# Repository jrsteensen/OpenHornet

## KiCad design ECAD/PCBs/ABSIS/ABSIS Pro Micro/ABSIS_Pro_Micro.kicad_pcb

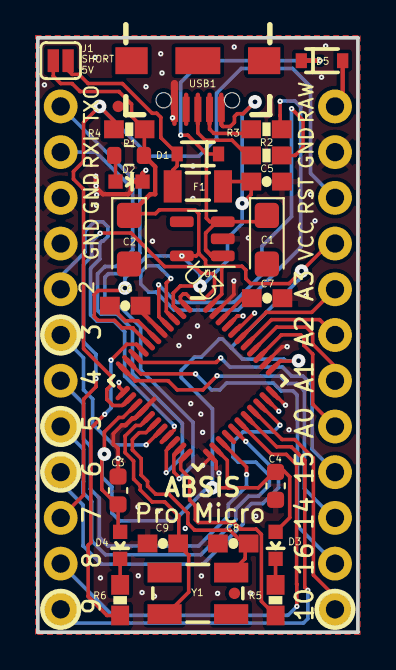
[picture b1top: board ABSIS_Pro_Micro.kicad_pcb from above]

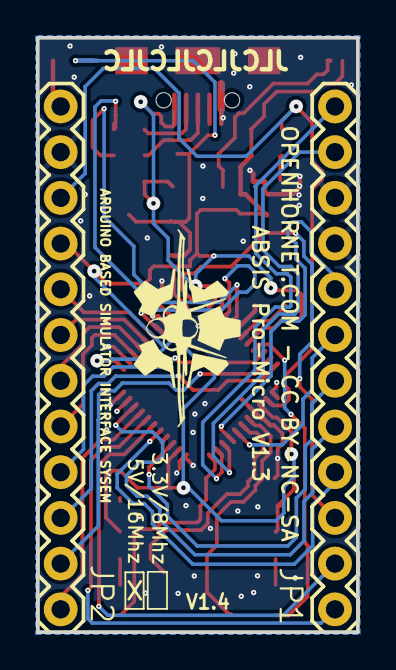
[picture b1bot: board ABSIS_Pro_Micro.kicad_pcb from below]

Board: 2 copper layers, 17.8 x 33.0 mm, 34 parts (3 on the bottom side), 38 nets.

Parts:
C1, C2: 10uF; CP_EIA-3216-18_Kemet-A
C3: 1uF; C_0603_1608Metric
C4: 0.1uF; C_0603_1608Metric
C5, C6: 1uF; 0603-CAP
C7: 0.1uF; 0603-CAP
C8, C9: 22pF; 0603-CAP
D1, D5: 1N4448WX-TP; SOD-323
D2: Red; LED-0603
D3: Green; LED-0603
D4: Yellow; LED-0603
F1: 500mA; PTC-1206
FRAME1, FRAME1#2: FRAME-LETTER; CREATIVE_COMMONS
JP1, JP2: M12PTH; 1X12
JP3, JP6: FIDUCIALUFIDUCIAL; MICRO-FIDUCIAL
JP4: LOGO-SFESK; SFE-LOGO-FLAME
LOGO: LOGO; LOGO_OH_NoText_Small
R1: 1K; R_0603_1608Metric
R2, R3: 22; 0603-RES
R4: 10K; 0603-RES
R5, R6: 330; 0603-RES
SJ1: SOLDERJUMPERNC; SJ_2S
U1: MIC5219; SOT-23-5
U3: ATMEGA32U4; QFN-44-NOPAD_1_1-OUTFAKES
USB1: ZX62-AB-5PA(31); USB-AB-MICRO-SMD-V03-IN&OUT
Y1: 16MHz; CRYSTAL-SMD-5X3

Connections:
+5V: C3.1, C4.2, C5.2, D3.A, D4.A, F1.1, JP2.4, R1.2, R4.2, U1.5 (OUT), U3.2 (UVCC), U3.7 (VBUS), U3.14 (VCC@14), U3.24 (AVCC@24), U3.34 (VCC@34), U3.44 (AVCC@44), USB1.VBUS1 (VBUS)
/A0: JP2.8, U3.36 (PF7(ADC7))
/A1: JP2.7, U3.37 (PF6(ADC6))
/A2: JP2.6, U3.38 (PF5(ADC5))
/A3: JP2.5, U3.39 (PF4(ADC4))
/AREF: C7.2, U3.42 (AREF)
/D2: JP1.8, U3.19 (PD1(SDA))
/D3: JP1.7, U3.18 (PD0(SCL))
/D4: JP1.6, U3.25 (PD4(ADC8))
/D5: JP1.5, U3.31 (PC6)
/D6: JP1.4, U3.27 (PD7(ADC10))
/D7: JP1.3, U3.1 (PE6)
/D8: JP1.2, U3.28 (PB4(ADC11))
/D9: JP1.1, U3.29 (PB5(ADC12))
/D10: JP2.12, U3.30 (PB6(ADC13))
/D14: R6.1, U3.8 (PB3(MISO))
/D+: R2.1, U3.4 (D+)
/D-: R3.1, U3.3 (D-)
/MISO: JP2.10, U3.11 (PB0(SS))
/MOSI: JP2.11, U3.10 (PB2(MOSI))
/RAW: D5.2 (A), JP2.1
/RESET: JP2.3, R4.1, U3.13 (~RESET)
/RXI: JP1.11, U3.20 (PD2(RX))
/SCK: JP2.9, U3.9 (PB1(SCK))
/TXO: JP1.12, U3.21 (PD3(TX))
GND: C3.2, C4.1, C5.1, C6.1, C7.1, C8.2, C9.2, D2.C, JP1.9, JP1.10, JP2.2, U1.2 (GND), U3.5 (UGND), U3.15 (GND@15), U3.23 (GND@23), U3.33 (PE2/~HWB), U3.35 (GND@35), U3.43 (GND@43), USB1.GND1 (GND)
unnamed: D1.1 (C), D5.1 (C), U1.1 (IN), U1.3 (EN)
unnamed: D1.2 (A), SJ1.2
unnamed: D2.A, R1.1
unnamed: D3.C, R5.2
unnamed: D4.C, R6.2
unnamed: F1.2, SJ1.1
unnamed: R5.1, U3.22 (PD5)
unnamed: C6.2, U3.6 (UCAP)
unnamed: C8.1, U3.17 (XTAL1), Y1.3 (2)
unnamed: C9.1, U3.16 (XTAL2), Y1.1
unnamed: R2.2, USB1.D+1 (D+)
unnamed: R3.2, USB1.D-1 (D-)

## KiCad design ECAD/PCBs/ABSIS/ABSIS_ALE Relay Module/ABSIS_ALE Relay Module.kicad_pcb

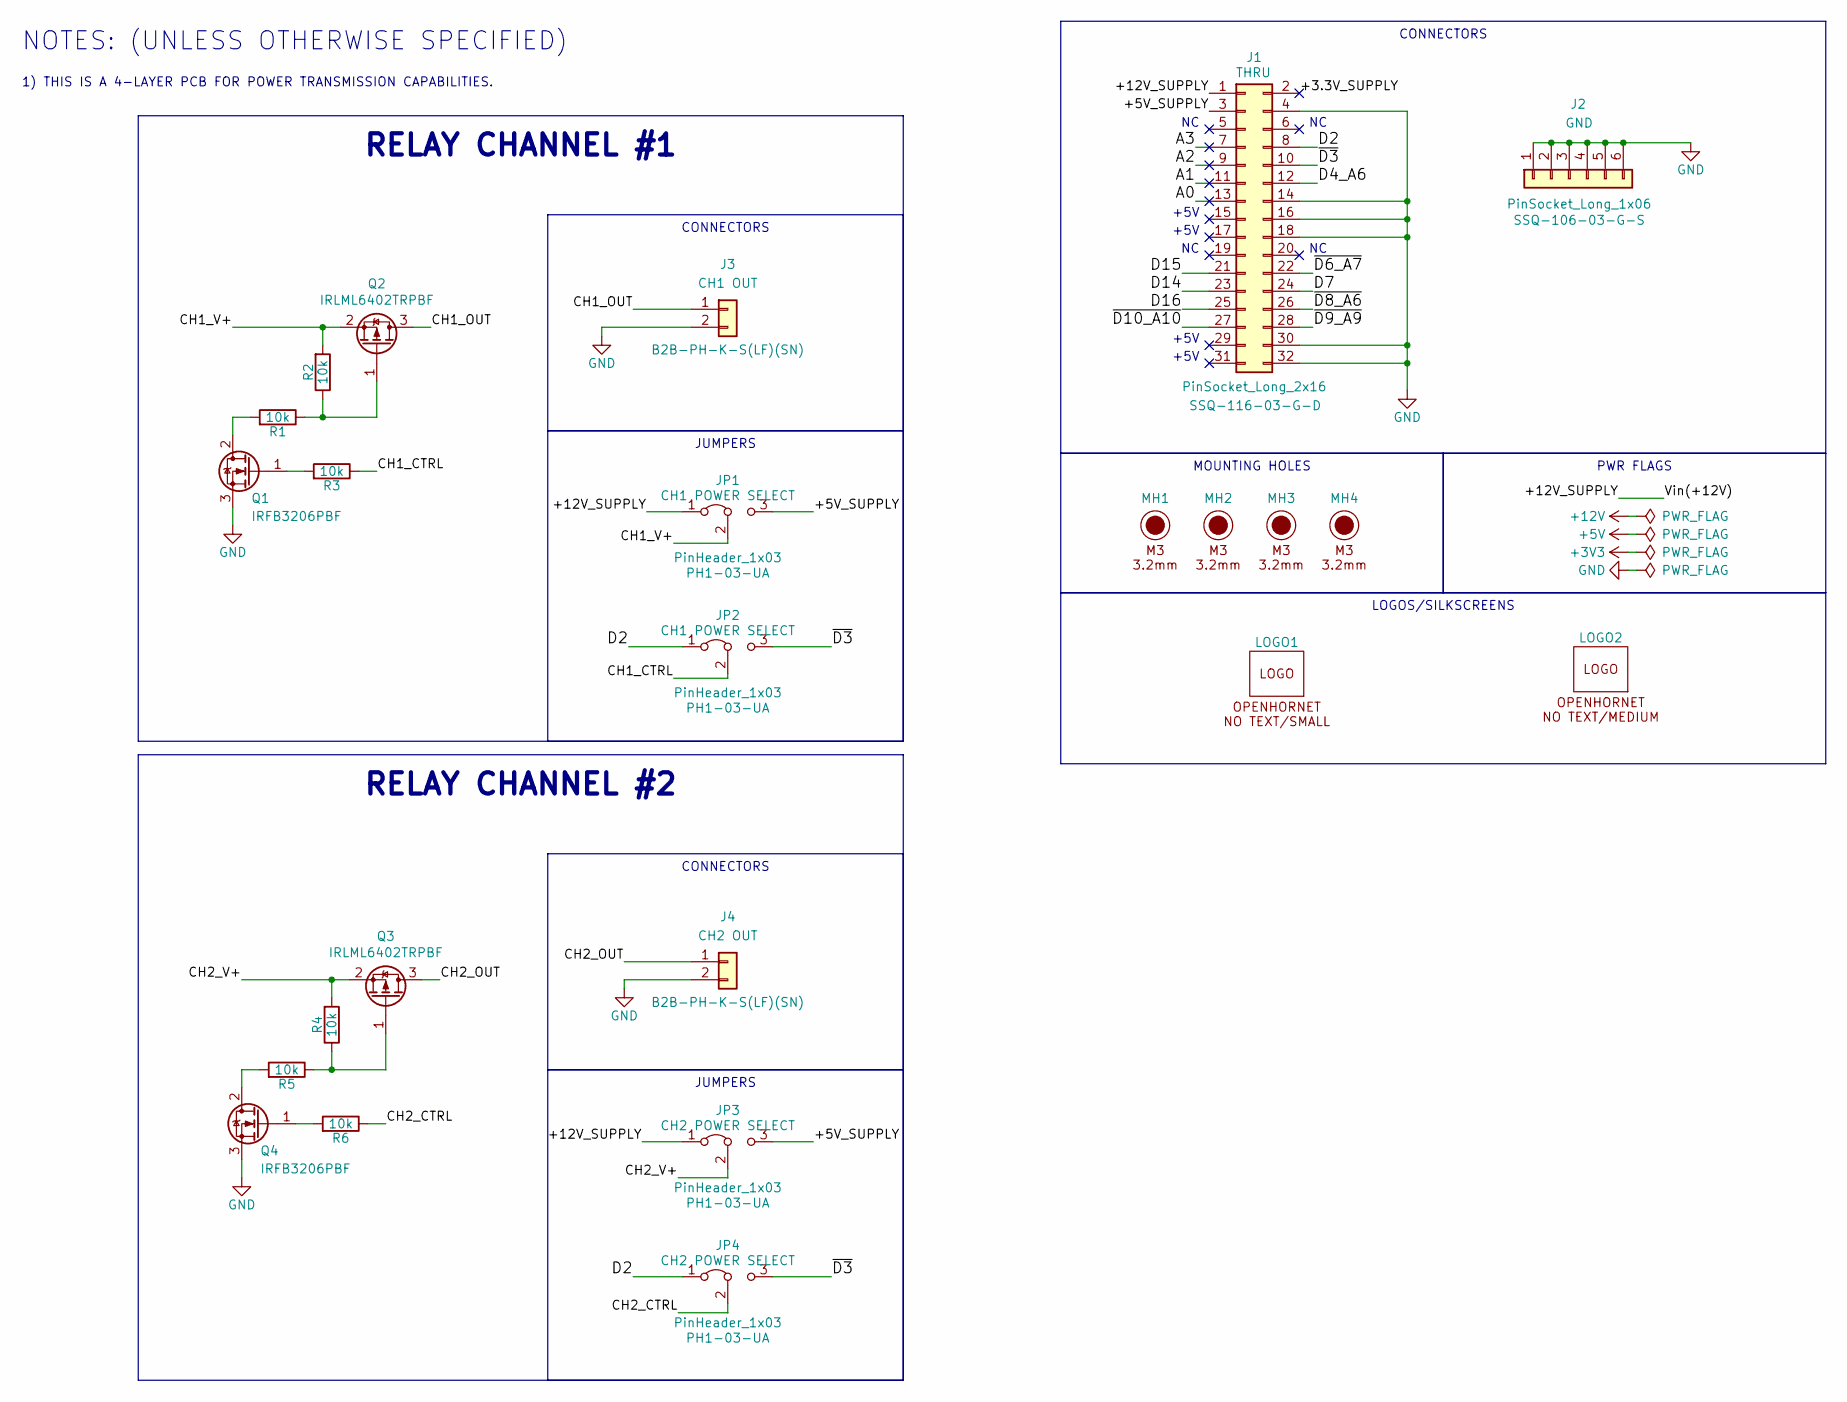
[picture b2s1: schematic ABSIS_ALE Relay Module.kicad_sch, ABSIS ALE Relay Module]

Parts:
J1: PinSocket_Long_2x16; PinSocket_2x16_P2.54mm_Vertical; Manufacturer PN SSQ-116-03-G-D
J2: PinSocket_Long_1x06; PinSocket_1x06_P2.54mm_Vertical; Manufacturer PN SSQ-106-03-G-S
J3, J4: JST_PH_01x02; JST_PH_B2B-PH-K_1x02_P2.00mm_Vertical; Manufacturer PN B2B-PH-K-S(LF)(SN)
JP1, JP2, JP3, JP4: PinHeader_1x03; PinHeader_1x03_P2.54mm_Vertical; Manufacturer PN PH1-03-UA
LOGO1: LOGO; LOGO_OH_NoText_Small
LOGO2: LOGO; LOGO_OH_NoText_Medium
MH1, MH2, MH3, MH4: M3 / 3.2mm; MountingHole_3.2mm_M3_DIN965
Q1, Q4: IRFB3206PBF; TO-220-3_Vertical; Manufacturer PN IRFB3206PBF; LCSC C2642
Q2, Q3: IRLML6402TRPBF; SOT-23; Manufacturer PN IRLML6402TRPBF; LCSC C2593
R1, R2, R3, R4, R5, R6: 10k; R_0603_1608Metric; Manufacturer PN 0603WAF1002T5E; LCSC C25804

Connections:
/+3.3V_SUPPLY: J1.2
/+5V_SUPPLY: J1.3, JP1.3 (B), JP3.3 (B)
/+12V_SUPPLY: J1.1, JP1.1 (A), JP3.1 (A)
/A0: J1.13
/A1: J1.11
/A2: J1.9
/A3: J1.7
/CH1_CTRL: JP2.2 (C), R3.1
/CH1_OUT: J3.1, Q2.3 (D)
/CH1_V+: JP1.2 (C), Q2.2 (S), R2.2
/CH2_CTRL: JP4.2 (C), R6.1
/CH2_OUT: J4.1, Q3.3 (D)
/CH2_V+: JP3.2 (C), Q3.2 (S), R4.2
/D2: J1.8, JP2.1 (A), JP4.1 (A)
/D4_A6: J1.12
/D7: J1.24
/D14: J1.23
/D15: J1.21
/D16: J1.25
/~D3: J1.10, JP2.3 (B), JP4.3 (B)
/~D6_A7: J1.22
/~D8_A6: J1.26
/~D9_A9: J1.28
/~D10_A10: J1.27
GND: J1.4, J1.14, J1.16, J1.18, J1.30, J1.32, J2.1, J2.2, J2.3, J2.4, J2.5, J2.6, J3.2, J4.2, Q1.3 (S), Q4.3 (S)
unnamed: Q1.2 (D), R1.2
unnamed: Q1.1 (G), R3.2
unnamed: Q2.1 (G), R1.1, R2.1
unnamed: Q3.1 (G), R4.1, R5.1
unnamed: Q4.2 (D), R5.2
unnamed: Q4.1 (G), R6.2

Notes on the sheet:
RELAY CHANNEL #1
CONNECTORS
JUMPERS
PWR FLAGS
LOGOS/SILKSCREENS
MOUNTING HOLES
RELAY CHANNEL #2
+5V
1) THIS IS A 4-LAYER PCB FOR POWER TRANSMISSION CAPABILITIES.
NOTES: (UNLESS OTHERWISE SPECIFIED)

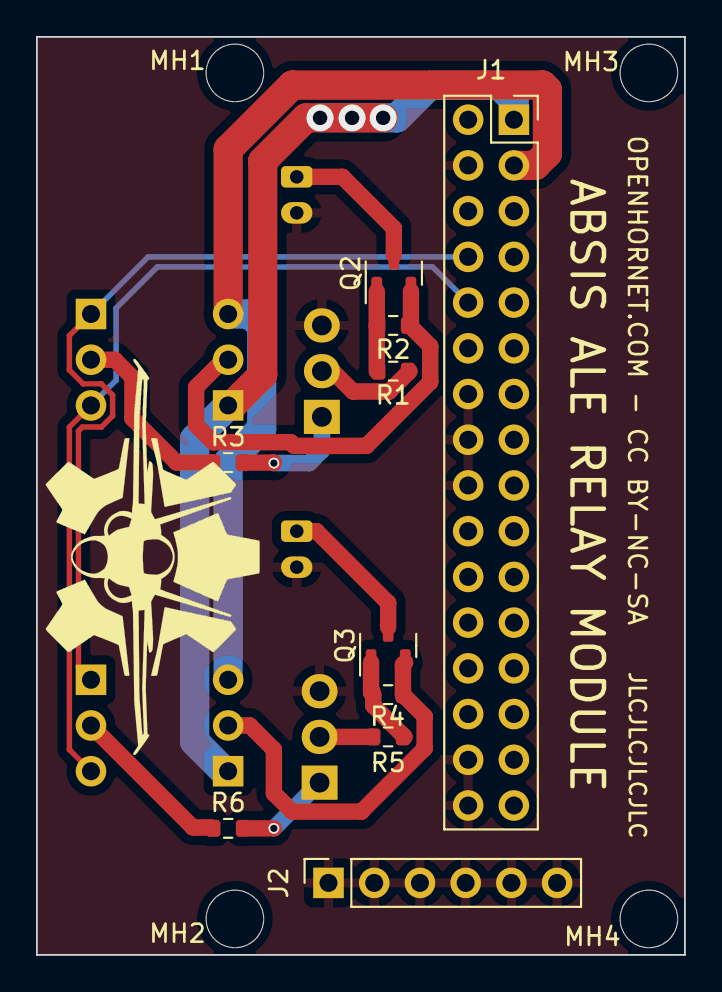
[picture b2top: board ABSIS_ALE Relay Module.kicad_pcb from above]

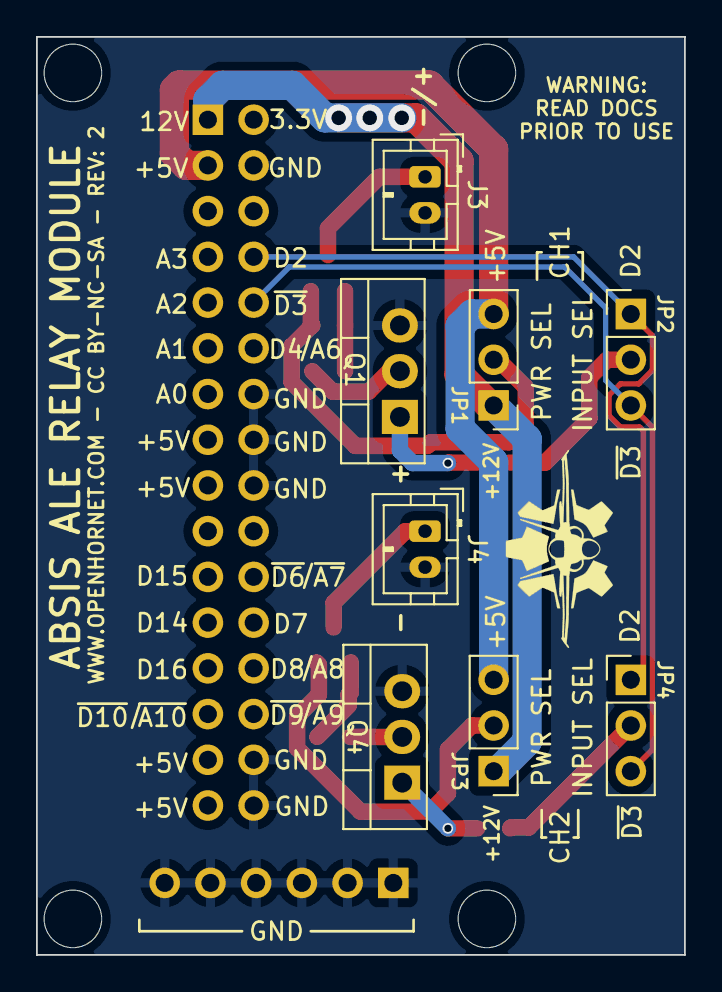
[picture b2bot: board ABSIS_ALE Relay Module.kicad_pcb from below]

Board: 2 copper layers, 36.0 x 51.0 mm, 24 parts (9 on the bottom side), 17 nets.

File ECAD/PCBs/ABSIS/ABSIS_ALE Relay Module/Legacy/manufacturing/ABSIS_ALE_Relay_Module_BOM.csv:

Comment,Designator,Footprint,LCSC
"MH","H1,H2,H3,H4","MountingHole:MountingHole_3.2mm_M3_DIN965",""
"THRU","J1","Connector_PinSocket_2.54mm:PinSocket_2x16_P2.54mm_Vertical",""
"GND","J2","Connector_PinSocket_2.54mm:PinSocket_1x06_P2.54mm_Vertical",""
"CH1 OUT","J3","Connector_JST:JST_PH_B2B-PH-K_1x02_P2.00mm_Vertical",""
"CH2 OUT","J4","Connector_JST:JST_PH_B2B-PH-K_1x02_P2.00mm_Vertical",""
"CH1 PWR SEL","JP1","Connector_PinHeader_2.54mm:PinHeader_1x03_P2.54mm_Vertical",""
"CH1 SEL A","JP2","Connector_PinHeader_2.54mm:PinHeader_1x03_P2.54mm_Vertical",""
"CH2 PWR SEL","JP4","Connector_PinHeader_2.54mm:PinHeader_1x03_P2.54mm_Vertical",""
"CH2 SEL A","JP5","Connector_PinHeader_2.54mm:PinHeader_1x03_P2.54mm_Vertical",""
"OpenHornetLogoSmall","LOGO1","KiCAD Libraries:OH_LOGO_ONLY_11x6mm",""
"IRLML6402TRPBF","Q2,Q3","Package_TO_SOT_SMD:SOT-23","C2593"
"IRFB3206PBF","Q1,Q4","Package_TO_SOT_THT:TO-220-3_Vertical","C2642"
"10K","R1,R2,R3,R4,R5,R6","Resistor_SMD:R_0603_1608Metric_Pad0.98x0.95mm_HandSolder","C25804"

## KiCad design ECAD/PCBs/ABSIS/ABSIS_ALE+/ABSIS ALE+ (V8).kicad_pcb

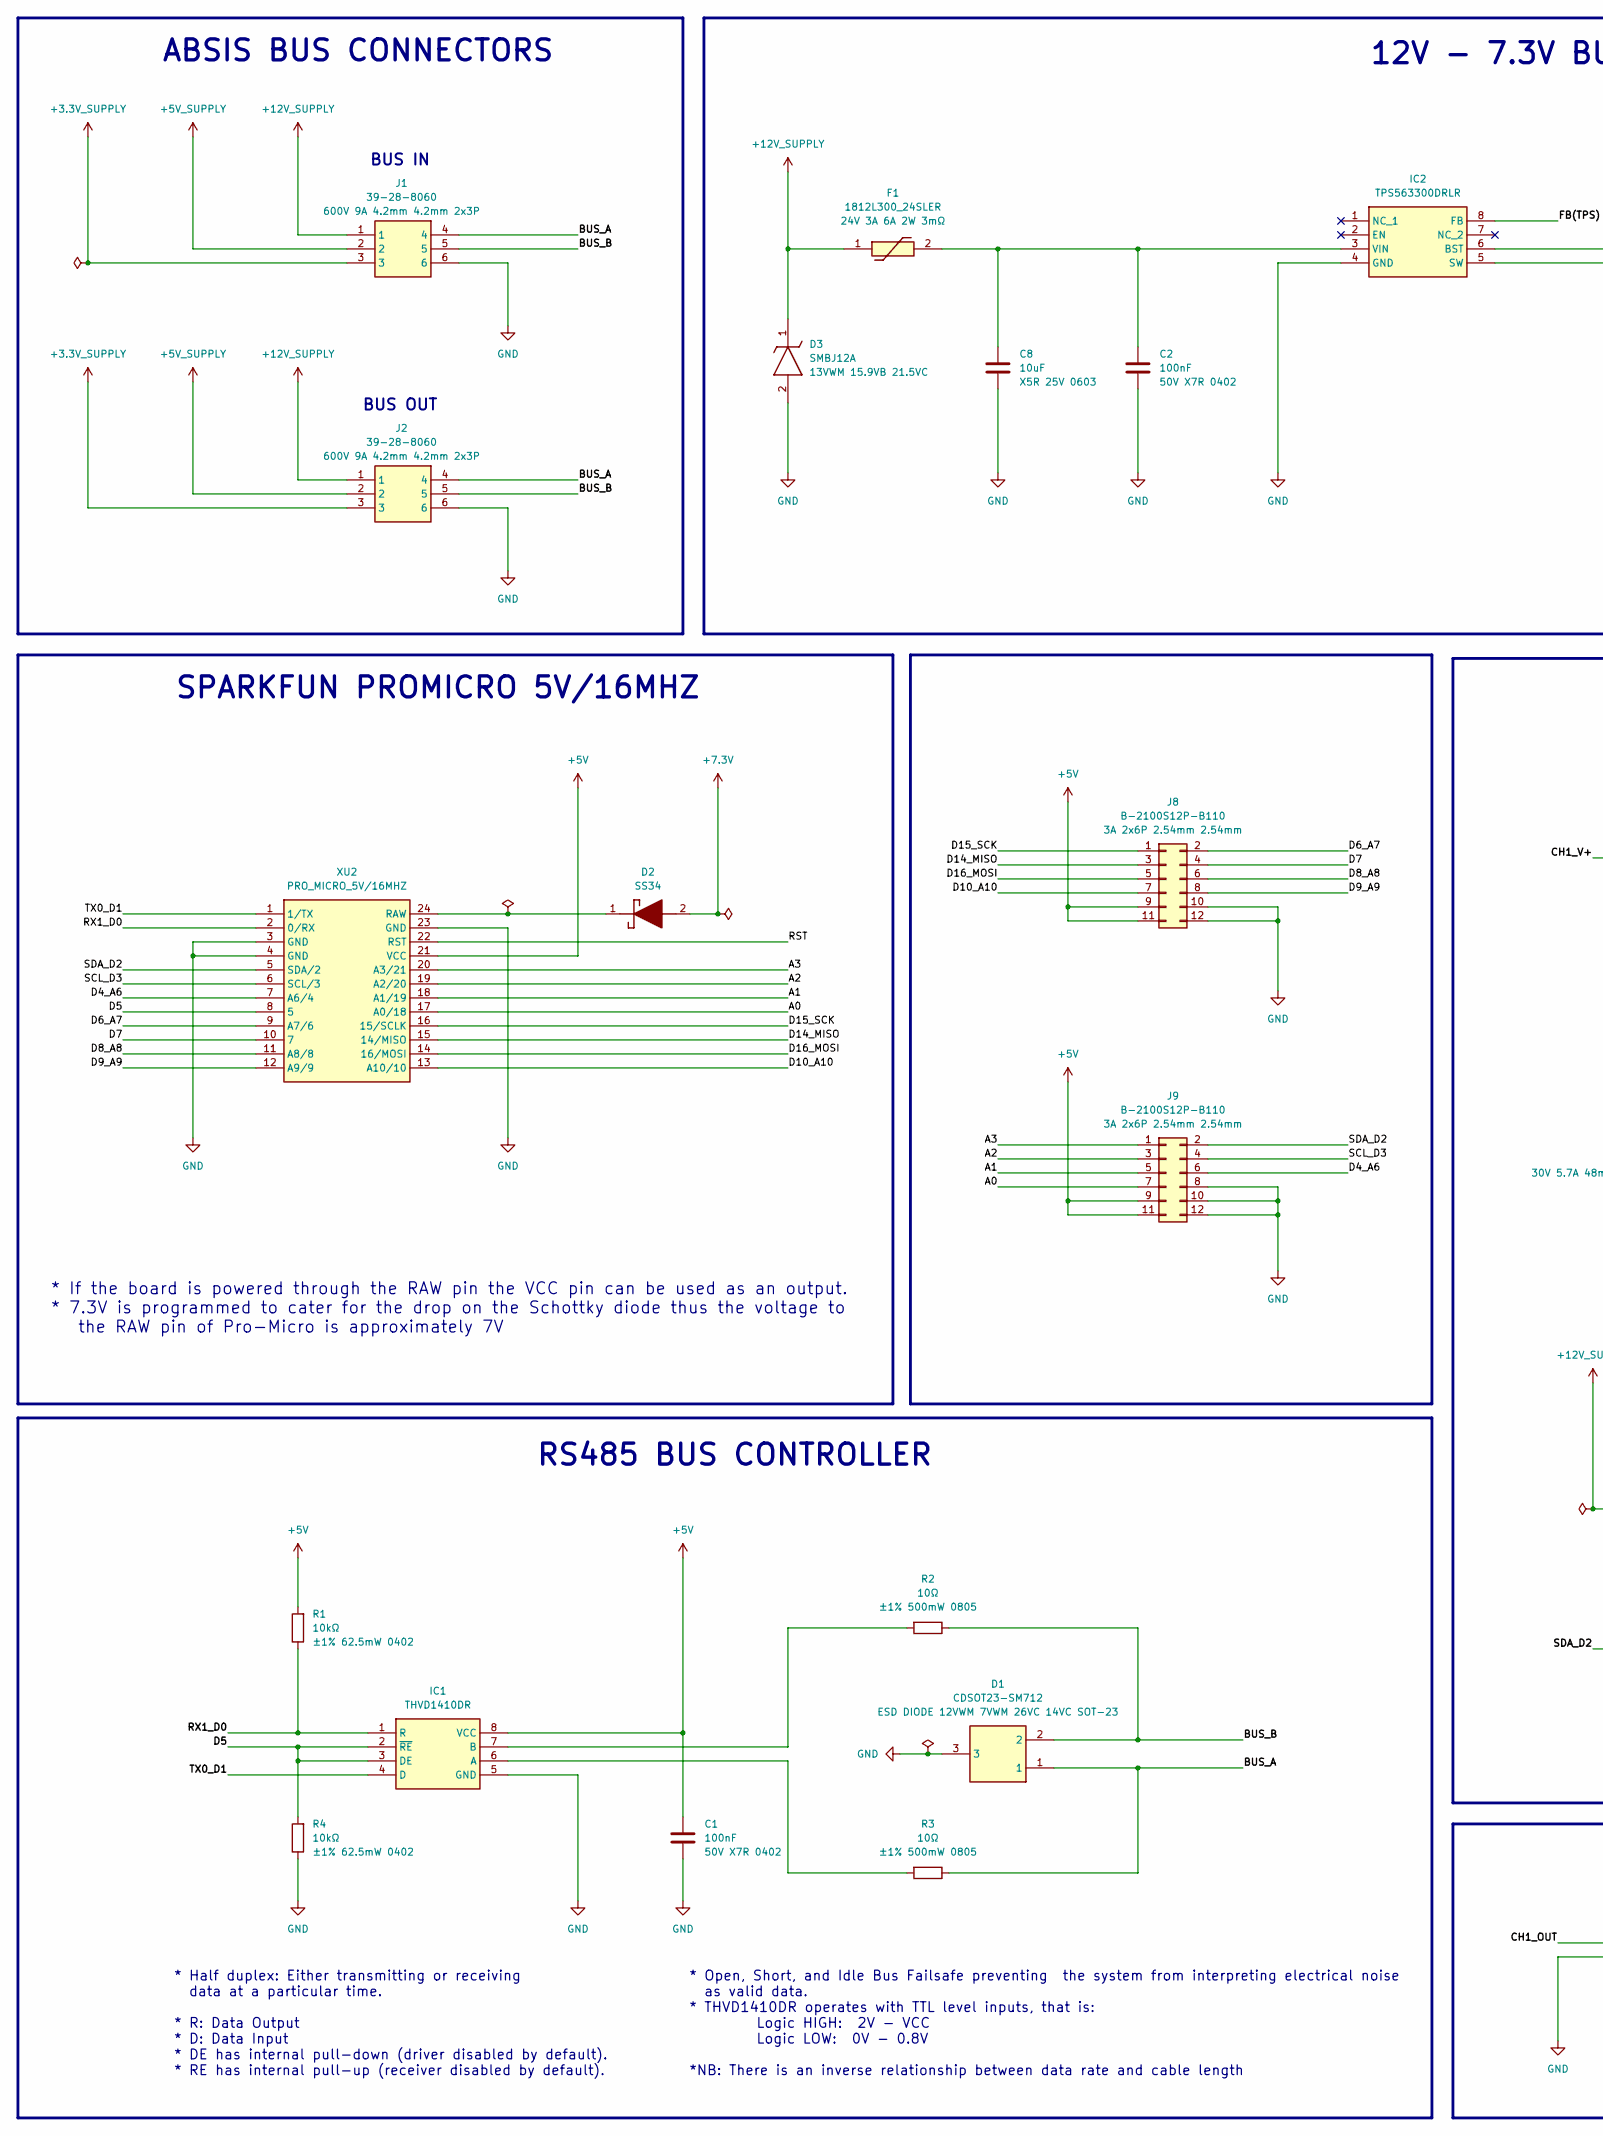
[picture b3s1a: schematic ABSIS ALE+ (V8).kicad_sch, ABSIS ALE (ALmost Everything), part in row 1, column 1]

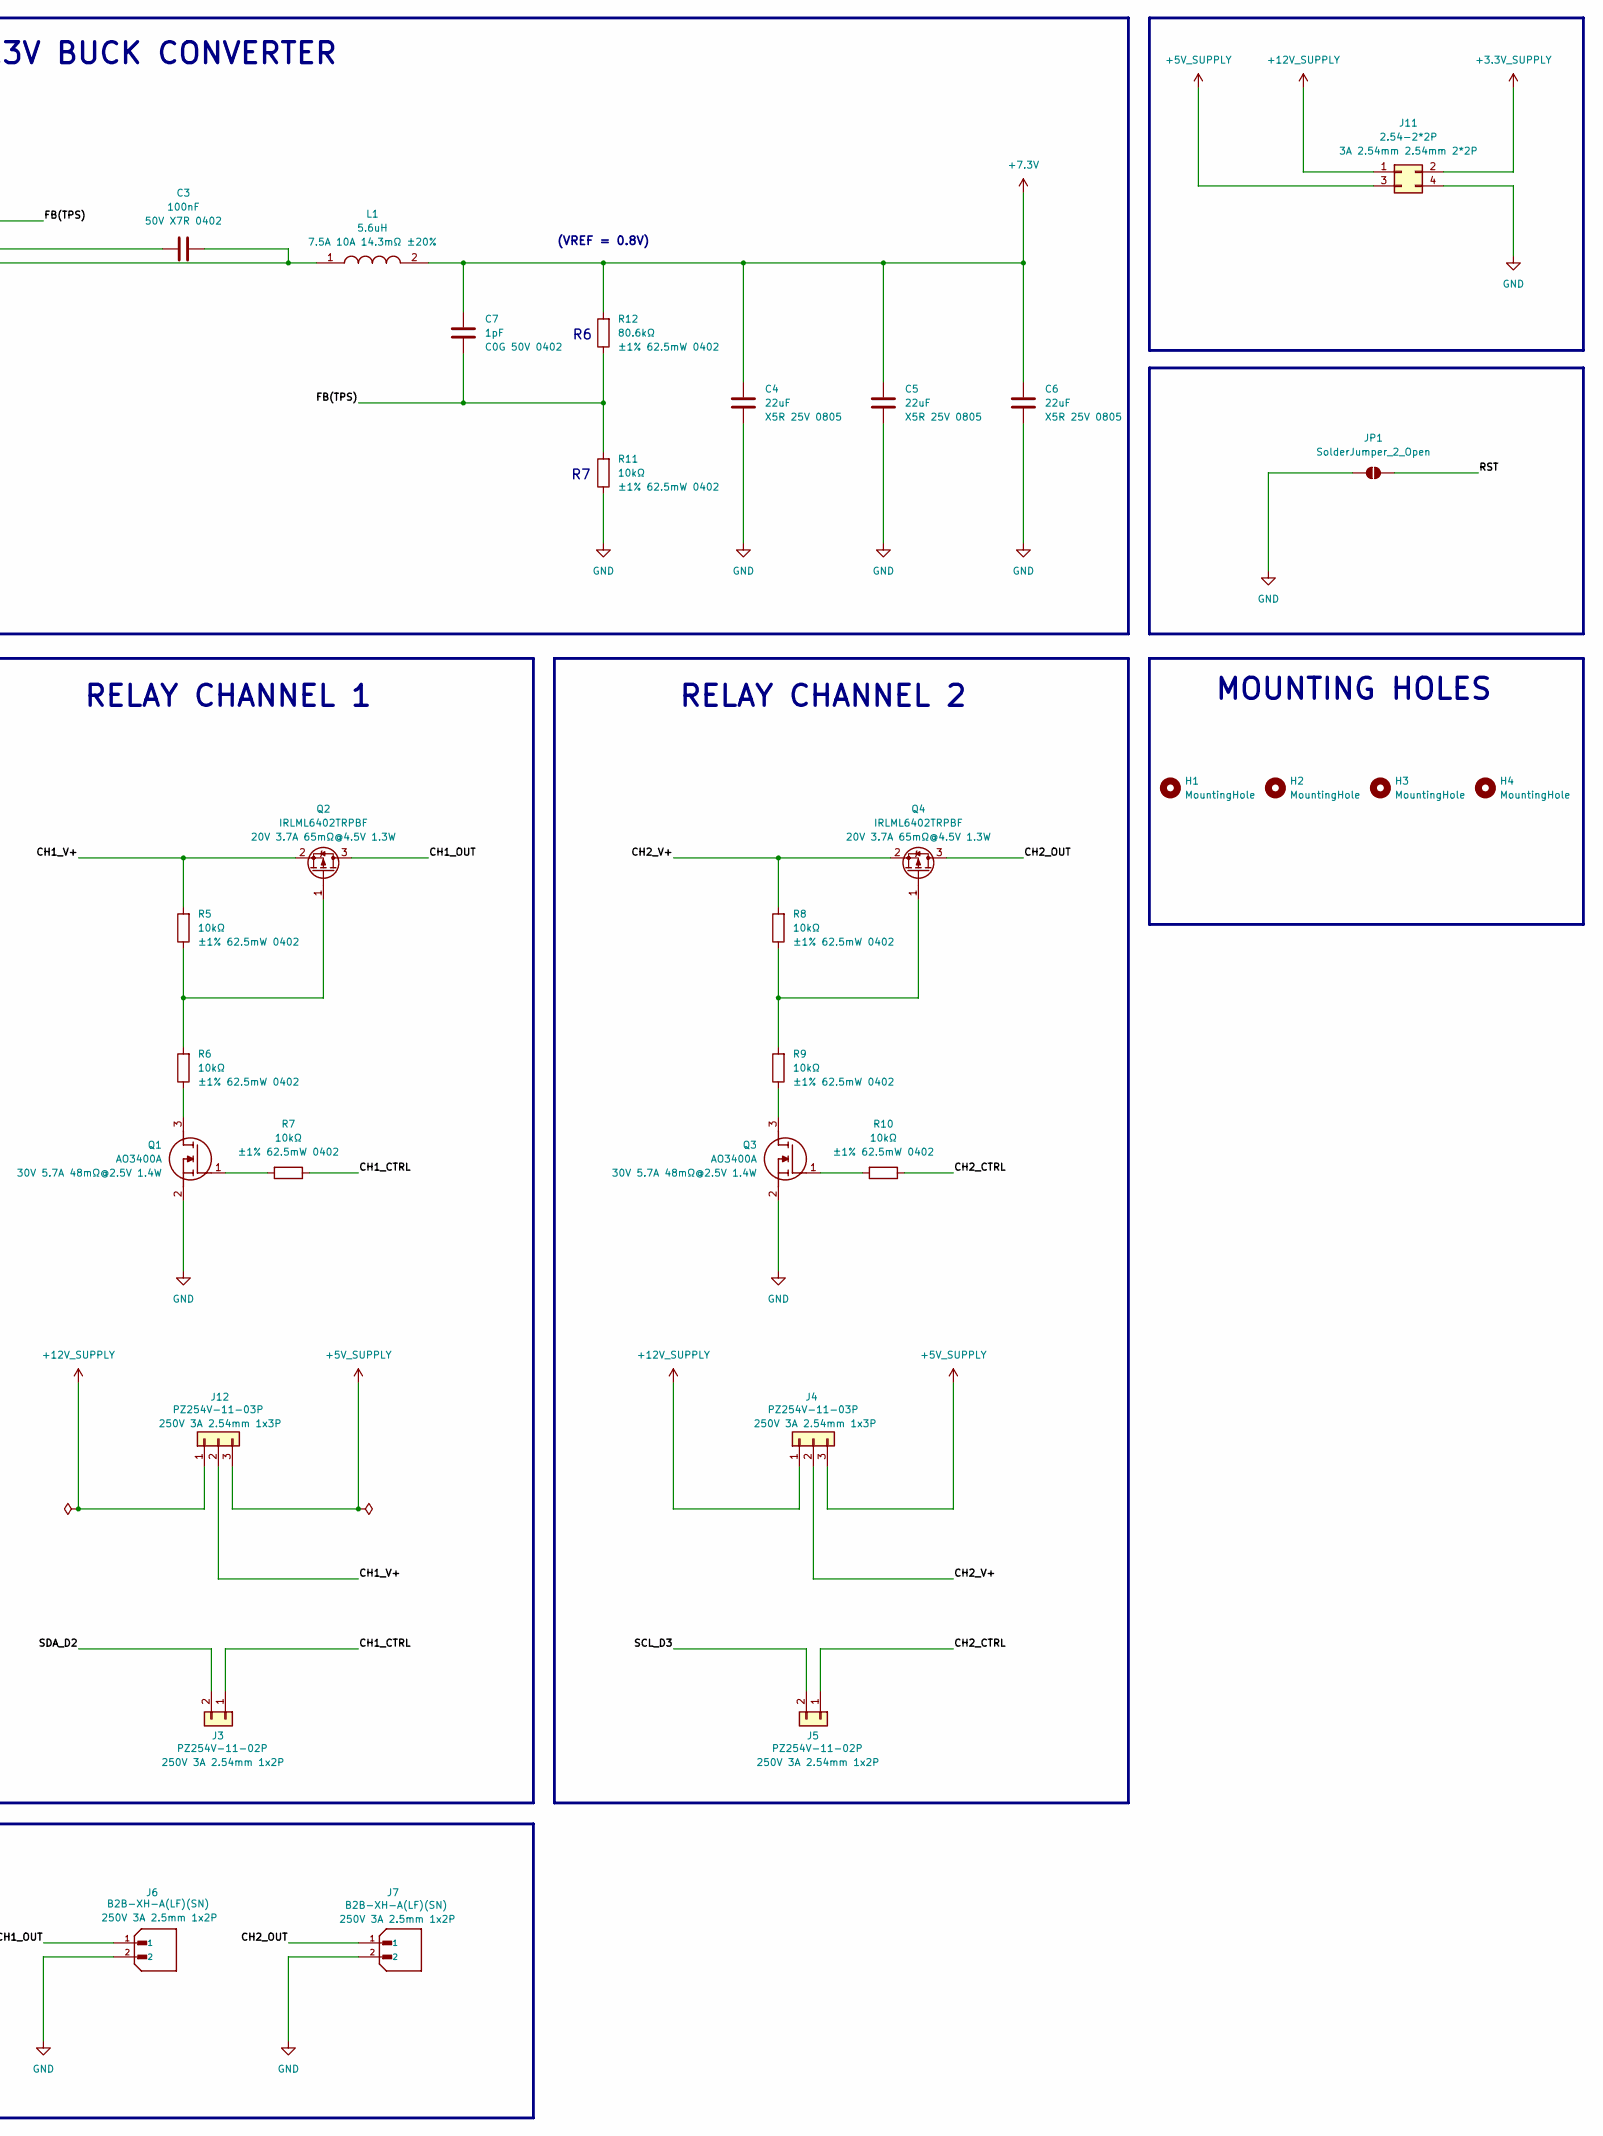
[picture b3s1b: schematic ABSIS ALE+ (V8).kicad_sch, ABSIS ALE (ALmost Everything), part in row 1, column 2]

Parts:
C1, C2, C3: 100nF; C_0402_1005Metric; Manufacturer PN CL05B104KB54PNC; LCSC C307331
C4, C5, C6: 22uF; C_0805_2012Metric; Manufacturer PN CL21A226MAQNNNE; LCSC C45783
C7: 1pF; C_0402_1005Metric; Manufacturer PN 0402CG1R0C500NT; LCSC C1550
C8: 10uF; C_0603_1608Metric; Manufacturer PN CL10A106MA8NRNC; LCSC C96446
D1: CDSOT23-SM712; Manufacturer PN CDSOT23-SM712; LCSC C404012
D2: SS34; Manufacturer PN SS34; LCSC C8678
D3: SMBJ12A; Manufacturer PN SMBJ12A; LCSC C151251
F1: 1812L300_24SLER; Manufacturer PN 1812L300/24SLER; LCSC C1512049
H1, H2, H3, H4: MountingHole; MountingHole_3.2mm_M3_DIN965
IC1: THVD1410DR; Manufacturer PN THVD1410DR; LCSC C2671345
IC2: TPS563300DRLR; Manufacturer PN TPS563300DRLR; LCSC C5219249
J1, J2: 39-28-8060; Manufacturer PN 39288060; LCSC C505058
J3, J5: PZ254V-11-02P; PinHeader_1x02_P2.54mm_Vertical; Manufacturer PN PZ254V-11-02P; LCSC C492401
J4, J12: PZ254V-11-03P; PinHeader_1x03_P2.54mm_Vertical; Manufacturer PN PZ254V-11-03P; LCSC C2937625
J6, J7: B2B-XH-A(LF)(SN); B2B-XH-A__LF__SN_; Manufacturer PN B2B-XH-A(LF)(SN); LCSC C158012
J8, J9: B-2100S12P-B110; PinHeader_2x06_P2.54mm_Vertical; Manufacturer PN B-2100S12P-B110; LCSC C124388
J11: 2.54-2*2P; PinHeader_2x02_P2.54mm_Vertical; Manufacturer PN 2.54-2*2P; LCSC C66690
JP1: SolderJumper_2_Open; SolderJumper-2_P1.3mm_Open_RoundedPad1.0x1.5mm
L1: 5.6uH; SRP6060FA-5R6M; Manufacturer PN SRP6060FA-5R6M; LCSC C1332221
Q1, Q3: AO3400A; Manufacturer PN AO3400A; LCSC C20917
Q2, Q4: IRLML6402TRPBF; Manufacturer PN IRLML6402TRPBF; LCSC C2593
R1, R4, R5, R6, R7, R8, R9, R10, R11: 10kΩ; R_0402_1005Metric; Manufacturer PN 0402WGF1002TCE; LCSC C25744
R2, R3: 10Ω; R_0805_2012Metric; Manufacturer PN CRCW080510R0FKEAHP; LCSC C844598
R12: 80.6kΩ; R_0402_1005Metric; Manufacturer PN 0402WGF8062TCE; LCSC C25921
XU2: PRO_MICRO_5V/16MHZ; PRO_MICRO_5V16MHZ; Manufacturer PN PRO_MICRO_5V/16MHZ

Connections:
+3.3V_SUPPLY: J1.3, J2.3, J11.2
+5V: C1.2, IC1.8 (VCC), J8.9, J8.11, J9.9, J9.11, R1.2, XU2.21 (VCC)
+5V_SUPPLY: J1.2, J2.2, J4.3, J11.3, J12.3
+7.3V: C4.1, C5.1, C6.1, C7.1, D2.2 (A), L1.2, R12.2
+12V_SUPPLY: D3.1 (K), F1.1, J1.1, J2.1, J4.1, J11.1, J12.1
/A0: J9.7, XU2.17 (A0/18)
/A1: J9.5, XU2.18 (A1/19)
/A2: J9.3, XU2.19 (A2/20)
/A3: J9.1, XU2.20 (A3/21)
/BUS_A: D1.1, J1.4, J2.4, R3.1
/BUS_B: D1.2, J1.5, J2.5, R2.1
/CH1_CTRL: J3.1, R7.1
/CH1_OUT: J6.1, Q2.3
/CH1_V+: J12.2, Q2.2, R5.2
/CH2_CTRL: J5.1, R10.1
/CH2_OUT: J7.1, Q4.3
/CH2_V+: J4.2, Q4.2, R8.2
/D4_A6: J9.6, XU2.7 (A6/4)
/D5: IC1.2 (~RE), IC1.3 (DE), R4.2, XU2.8 (5)
/D6_A7: J8.2, XU2.9 (A7/6)
/D7: J8.4, XU2.10 (7)
/D8_A8: J8.6, XU2.11 (A8/8)
/D9_A9: J8.8, XU2.12 (A9/9)
/D10_A10: J8.7, XU2.13 (A10/10)
/D14_MISO: J8.3, XU2.15 (14/MISO)
/D15_SCK: J8.1, XU2.16 (15/SCLK)
/D16_MOSI: J8.5, XU2.14 (16/MOSI)
/FB(TPS): C7.2, IC2.8 (FB), R11.2, R12.1
/RST: JP1.2 (B), XU2.22 (RST)
/RX1_D0: IC1.1 (R), R1.1, XU2.2 (0/RX)
/SCL_D3: J5.2, J9.4, XU2.6 (SCL/3)
/SDA_D2: J3.2, J9.2, XU2.5 (SDA/2)
/TX0_D1: IC1.4 (D), XU2.1 (1/TX)
GND: C1.1, C2.1, C4.2, C5.2, C6.2, C8.1, D1.3, D3.2 (A), IC1.5 (GND), IC2.4 (GND), J1.6, J2.6, J6.2, J7.2, J8.10, J8.12, J9.8, J9.10, J9.12, J11.4, JP1.1 (A), Q1.2 (S), Q3.2 (S), R4.1, R11.1, XU2.3 (GND), XU2.4 (GND), XU2.23 (GND)
unnamed: D2.1 (K), XU2.24 (RAW)
unnamed: IC1.6 (A), R3.2
unnamed: IC1.7 (B), R2.2
unnamed: C3.2, IC2.6 (BST)
unnamed: C3.1, IC2.5 (SW), L1.1
unnamed: C2.2, C8.2, F1.2, IC2.3 (VIN)
unnamed: Q1.3 (D), R6.1
unnamed: Q1.1 (G), R7.2
unnamed: Q2.1, R5.1, R6.2
unnamed: Q3.3 (D), R9.1
unnamed: Q3.1 (G), R10.2
unnamed: Q4.1, R8.1, R9.2

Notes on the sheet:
BUS IN
(VREF = 0.8V)
BUS OUT
SPARKFUN PROMICRO 5V/16MHZ
12V - 7.3V BUCK CONVERTER
ABSIS BUS CONNECTORS
RELAY CHANNEL 1
* Open, Short, and Idle Bus Failsafe preventing the system from interpreting electrical noise as valid data. * THVD1410DR operates with TTL level inputs, that is: Logic HIGH: 2V - VCC Logic LOW: 0V - 0.8V *NB: There is an inverse relationship between data rate and cable length
RELAY CHANNEL 2
MOUNTING HOLES
RS485 BUS CONTROLLER
* If the board is powered through the RAW pin the VCC pin can be used as an output. * 7.3V is programmed to cater for the drop on the Schottky diode thus the voltage to the RAW pin of Pro-Micro is approximately 7V
* Half duplex: Either transmitting or receiving data at a particular time. * R: Data Output * D: Data Input * DE has internal pull-down (driver disabled by default). * RE has internal pull-up (receiver disabled by default).

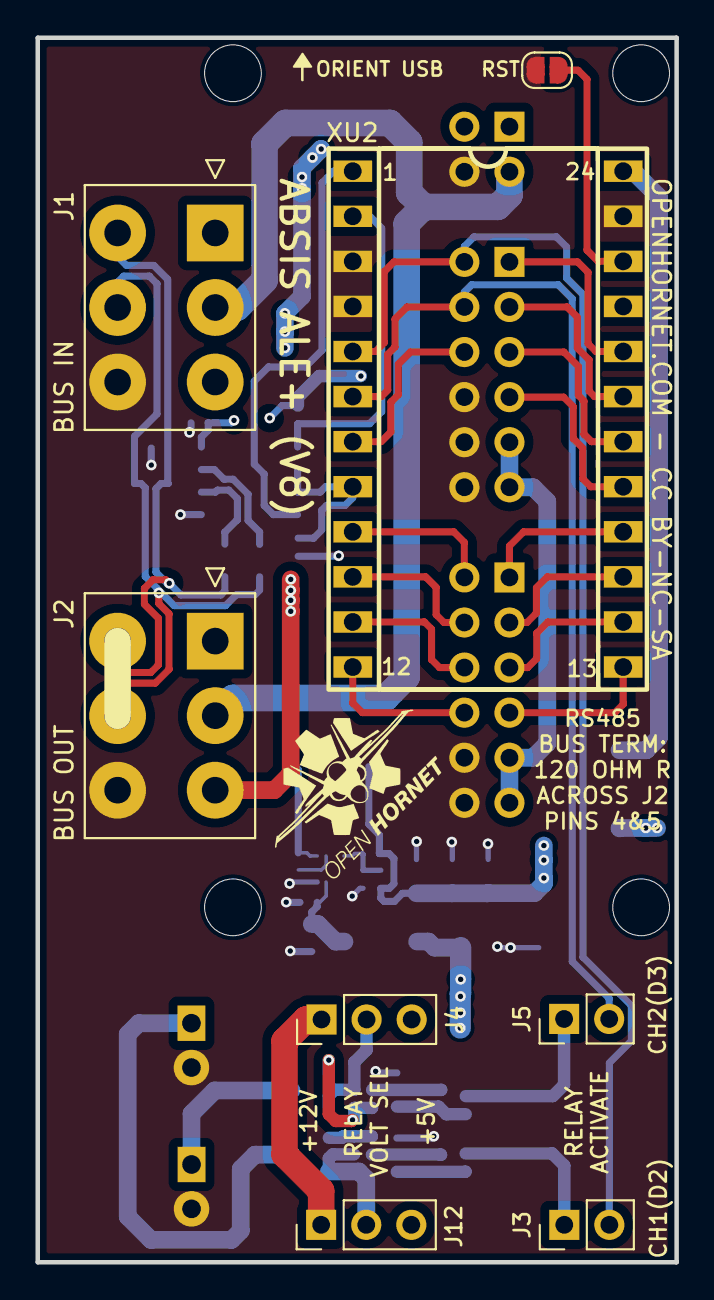
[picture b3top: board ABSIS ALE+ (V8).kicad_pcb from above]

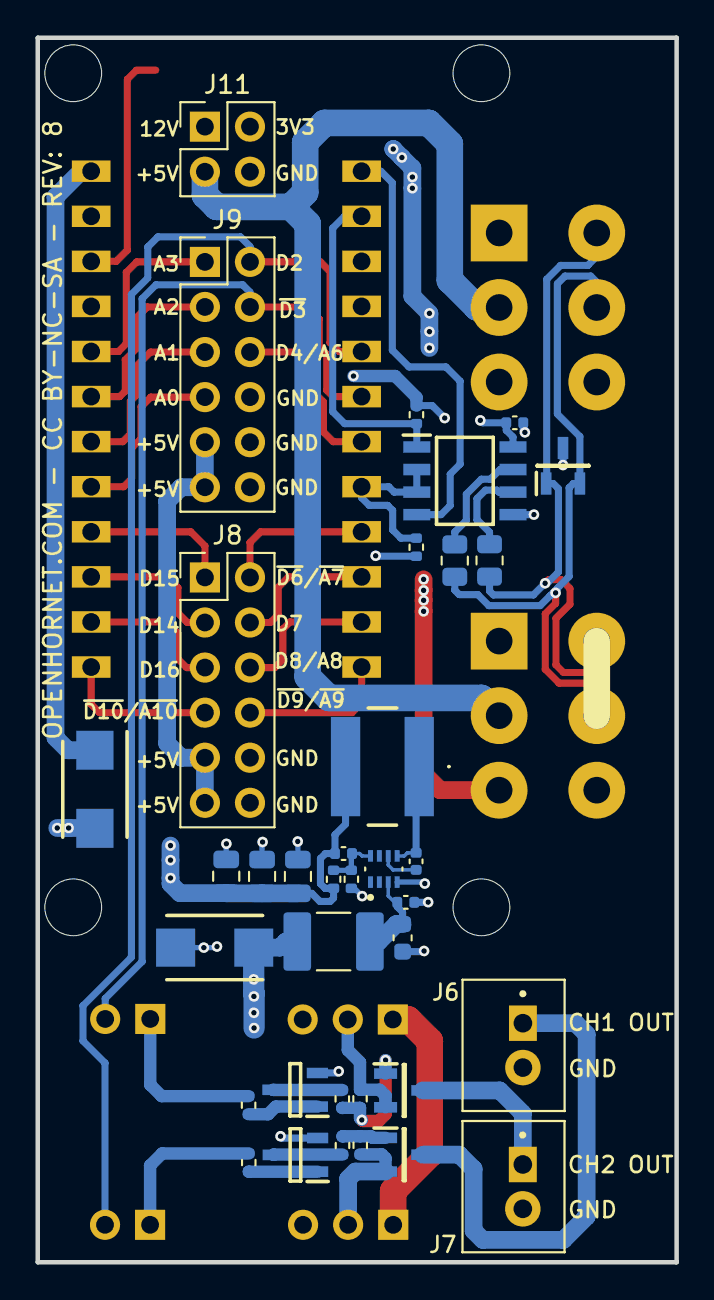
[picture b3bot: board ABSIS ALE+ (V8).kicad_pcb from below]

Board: 4 copper layers, 36.0 x 69.0 mm, 48 parts (36 on the bottom side), 46 nets.

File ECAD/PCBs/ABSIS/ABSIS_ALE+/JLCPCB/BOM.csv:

"Reference","Qty","Value","DNP","Exclude from BOM","Exclude from Board","Footprint","Datasheet","LCSC","Manufacturer PN","Manufacturer_Name","Description"
"C1,C2,C3","3","100nF","","","","Capacitor_SMD:C_0402_1005Metric","https://www.lcsc.com/datasheet/C307331.pdf?spm=wm.sxq.inf.gg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","C307331","CL05B104KB54PNC","","50V X7R 0402"
"C4,C5,C6","3","22uF","","","","Capacitor_SMD:C_0805_2012Metric","https://www.lcsc.com/datasheet/C45783.pdf?spm=wm.sxq.inf.ggs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","C45783","CL21A226MAQNNNE","","X5R 25V 0805"
"C7","1","1pF","","","","Capacitor_SMD:C_0402_1005Metric","https://www.lcsc.com/datasheet/C1550.pdf?spm=wm.sxq.inf.ggs&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","C1550","0402CG1R0C500NT","","C0G 50V 0402"
"C8","1","10uF","","","","Capacitor_SMD:C_0603_1608Metric","https://www.lcsc.com/datasheet/C96446.pdf?spm=wm.sxq.inf.ggs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","C96446","CL10A106MA8NRNC","","X5R 25V 0603"
"D1","1","CDSOT23-SM712","","","","CDSOT23-SM712:CDSOT23-SM712","http://uk.rs-online.com/web/p/products/7673728","C404012","CDSOT23-SM712","","ESD DIODE 12VWM 7VWM 26VC 14VC SOT-23"
"D2","1","SS34","","","","SS34:SS34","https://datasheet.lcsc.com/szlcsc/MDD-Jiangsu-Yutai-Elec-SS3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","C8678","SS34","MDD(Microdiode Semiconductor)","Schottky Barrier Diodes (SBD) SMA(DO-214AC) RoHS"
"D3","1","SMBJ12A","","","","SMBJ12A:SMBJ12A","https://www.littelfuse.com/~/media/electronics/datasheets/tv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","C151251","SMBJ12A","LITTELFUSE","13VWM 15.9VB 21.5VC"
"F1","1","1812L300_24SLER","","","","1812L300_24SLER:1812L300_24SLER","https://www.littelfuse.com/~/media/electronics/datasheets/re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","C1512049","1812L300/24SLER ","LITTELFUSE","24V 3A 6A 2W 3mΩ"
"H1,H2,H3,H4","4","MountingHole","","Excluded from BOM","","MountingHole:MountingHole_3.2mm_M3_DIN965","~","","","","Mounting Hole without connection"
"IC1","1","THVD1410DR","","","","THVD1410DR:THVD1410DR","http://www.ti.com/lit/gpn/THVD1410","C2671345","THVD1410DR","","3.3-V to 5-V RS-485 transceiver with +/-18-kV IEC ESD protection"
"IC2","1","TPS563300DRLR","","","","TPS563300DRLR:TPS563300DRLR","https://www.ti.com/lit/ds/symlink/tps563300.pdf?ts=166603599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","C5219249","TPS563300DRLR","","TPS563300 3.8-V to 28-V, 3-A Synchronous Buck Converter in SOT583 Package"
"J1,J2","2","39-28-8060","","","","39288060:39-28-8060","https://www.molex.com/pdm_docs/sd/039281023_sd.pdf","C505058","39288060","MOLEX","600V 9A 4.2mm 4.2mm 2x3P"
"J3,J5","2","PZ254V-11-02P","","","","Connector_PinHeader_2.54mm:PinHeader_1x02_P2.54mm_Vertical","https://www.lcsc.com/datasheet/C492401.pdf?spm=wm.sxq.inf.gg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","C492401","PZ254V-11-02P","XFCN","250V 3A 2.54mm 1x2P"
"J4,J12","2","PZ254V-11-03P","","","","Connector_PinHeader_2.54mm:PinHeader_1x03_P2.54mm_Vertical","https://www.lcsc.com/datasheet/C2937625.pdf?spm=wm.sxq.inf.g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","C2937625","PZ254V-11-03P","PZ254V-11-03P,XFCN","250V 3A 2.54mm 1x3P"
"J6,J7","2","B2B-XH-A(LF)(SN)","","","","B2B-XH-A(LF)(SN):B2B-XH-A__LF__SN_","https://www.lcsc.com/datasheet/C158012.pdf?spm=wm.sxq.inf.gg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","C158012","B2B-XH-A(LF)(SN)","JST","250V 3A 2.5mm 1x2P"
"J8,J9","2","B-2100S12P-B110","","","","Connector_PinHeader_2.54mm:PinHeader_2x06_P2.54mm_Vertical","https://www.lcsc.com/datasheet/C124388.pdf?spm=wm.sxq.inf.gg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","C124388","B-2100S12P-B110","Ckmtw","3A 2x6P 2.54mm 2.54mm"
"J11","1","2.54-2*2P","","","","Connector_PinHeader_2.54mm:PinHeader_2x02_P2.54mm_Vertical","https://www.lcsc.com/datasheet/C66690.pdf?spm=wm.sxq.inf.ggs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","C66690","2.54-2*2P","","3A 2.54mm 2.54mm 2*2P"
"JP1","1","SolderJumper_2_Open","","Excluded from BOM","","Jumper:SolderJumper-2_P1.3mm_Open_RoundedPad1.0x1.5mm","~","","","","Solder Jumper, 2-pole, open"
"L1","1","5.6uH","","","","SRP6060FA-5R6M:SRP6060FA-5R6M","https://www.bourns.com/docs/Product-Datasheets/SRP6060FA.pdf","C1332221","SRP6060FA-5R6M","Bourns","7.5A 10A 14.3mΩ ±20%"
"Q1,Q3","2","AO3400A","","","","AO3400A:AO3400A","http://aosmd.com/res/data_sheets/AO3400A.pdf","C20917","AO3400A","","30V 5.7A 48mΩ@2.5V 1.4W"
"Q2,Q4","2","IRLML6402TRPBF","","","","IRLML6402TRPBF:IRLML6402TRPBF","http://www.infineon.com/dgdl/irlml6402pbf.pdf?fileId=5546d46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","C2593","IRLML6402TRPBF","","20V 3.7A 65mΩ@4.5V 1.3W"
"R1,R4,R5,R6,R7,R8,R9,R10,R11","9","10kΩ","","","","Resistor_SMD:R_0402_1005Metric","https://www.lcsc.com/datasheet/C25744.pdf?spm=wm.sxq.inf.ggs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","C25744","0402WGF1002TCE","","±1% 62.5mW 0402"
"R2,R3","2","10Ω","","","","Resistor_SMD:R_0805_2012Metric","https://www.lcsc.com/datasheet/C844598.pdf?spm=wm.sxq.inf.gg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","C844598","CRCW080510R0FKEAHP","","±1% 500mW 0805"
"R12","1","80.6kΩ","","","","Resistor_SMD:R_0402_1005Metric","https://www.lcsc.com/datasheet/C25921.pdf?spm=wm.sxq.inf.ggs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","C25921","0402WGF8062TCE","","±1% 62.5mW 0402"
"XU2","1","PRO_MICRO_5V/16MHZ","","","","PRO_MICRO_5V16MHZ:PRO_MICRO_5V16MHZ","https://cdn.sparkfun.com/assets/f/d/8/0/d/ProMicro16MHzv2.pdf","","PRO_MICRO_5V/16MHZ","","PRO MICRO ATMEGA32U4 5V/16MHZ"

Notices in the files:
ECAD/PCBs/ABSIS/ABSIS Pro Micro/ABSIS_Pro_Micro.kicad_pcb:
OPENHORNET.COM - CC BY-NC-SA
ECAD/PCBs/ABSIS/ABSIS_ALE Relay Module/ABSIS_ALE Relay Module.kicad_pcb:
License:  CC BY-NC-SA
WWW.OPENHORNET.COM - CC BY-NC-SA - REV: 2
ECAD/PCBs/ABSIS/ABSIS_ALE+/ABSIS ALE+ (V8).kicad_pcb:
OPENHORNET.COM - CC BY-NC-SA - REV: 8
ECAD/PCBs/ABSIS/ABSIS_ALE/ABSIS_ALE.kicad_pcb:
OPENHORNET.COM - CC BY-NC-SA - REV: 3
ECAD/PCBs/ABSIS/ABSIS_ATX PSU Board/ATX PSU Board/ATX PSU Board.sch:
CC BY-NC-SA
parts and their libraries:
Released under the Creative Commons Attribution Share-Alike 3.0 License
